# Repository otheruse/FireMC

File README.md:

This is FireMC, a motion controller for RepRap 3D printers and Factory Robots like FirePick delta and others. FireMC is currently implemented as an Arduino Due add-on board. FireMC features:
- 12-30V input
- Separate heatbed input
- 12v 1.5A switching regulator for 12v peripherals (if input is not 12v)
- 7 pwm channels (1 heatbed, 3 high power, 1 med power and 2 channels connected to the 12v rail)
- Sockets for 6 stepper drivers
- micro-sd socket
- WiFi via esp8266 module
- 5 thermistor inputs
- 7 limit switch inputs
- 4 io's which can be used for thermocouple inputs and/or servos
- 2 expansion headers for LCD or other peripherals

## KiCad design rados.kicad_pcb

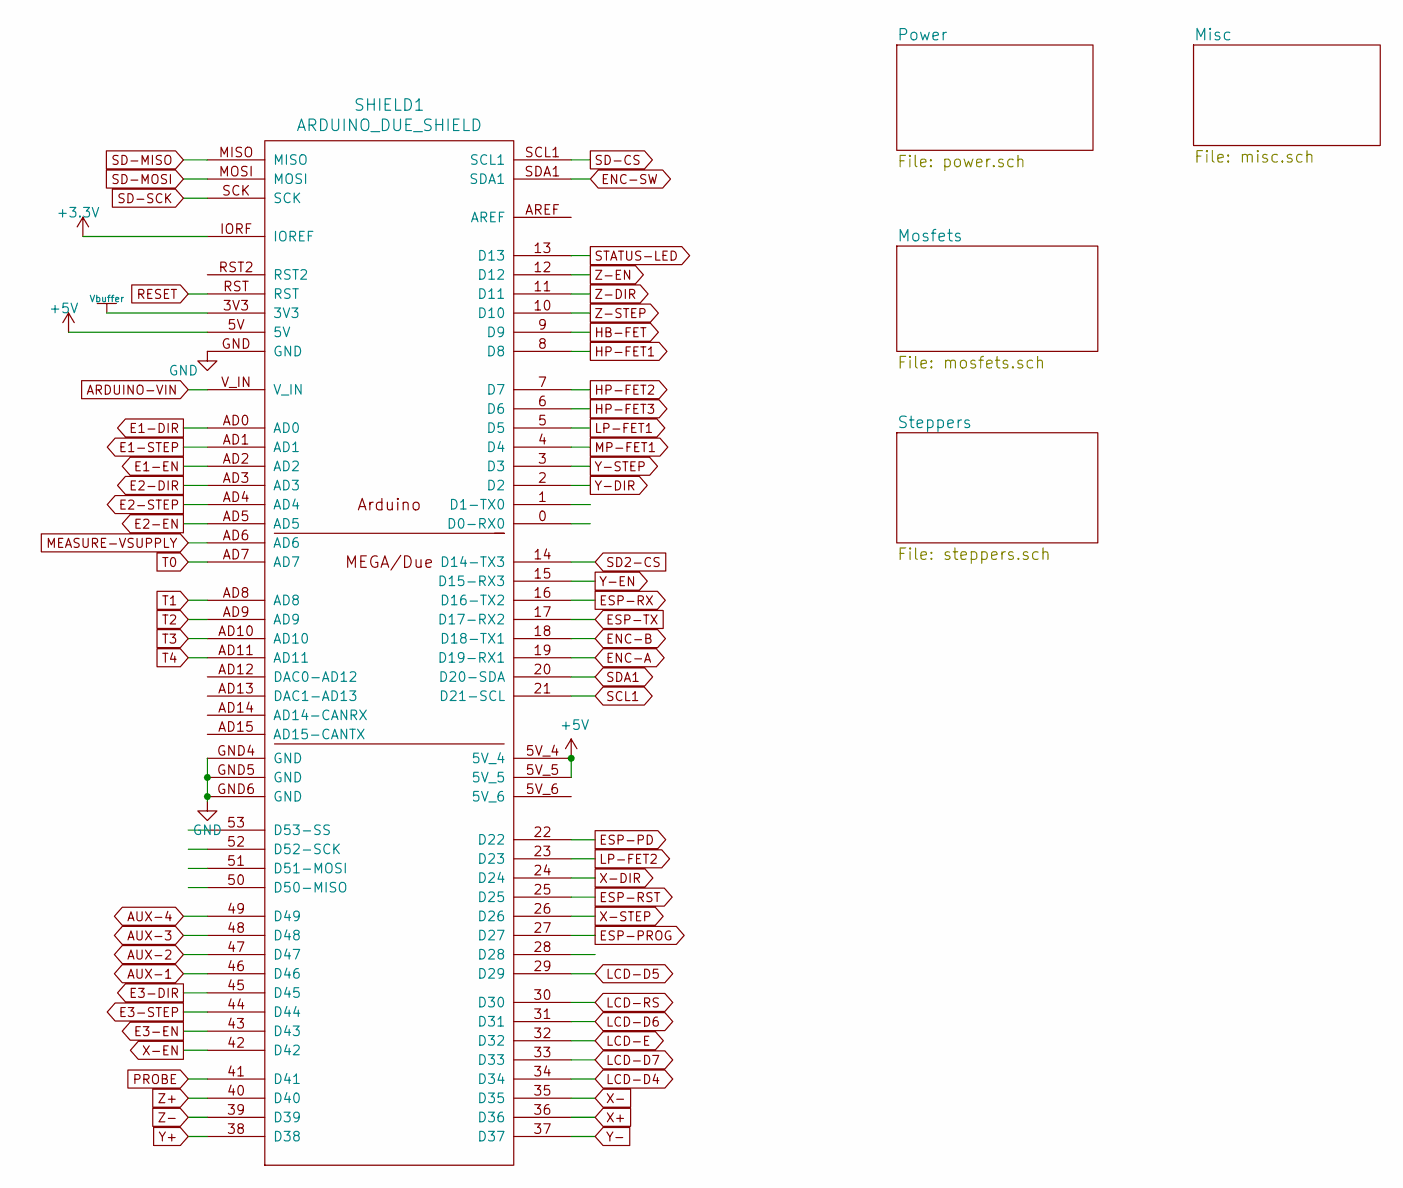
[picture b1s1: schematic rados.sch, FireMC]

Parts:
SHIELD1: ARDUINO_DUE_SHIELD; ARDUINO_MEGA_DUE_SHIELD_FOOTPRINT_OTH2

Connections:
+5V: SHIELD1.5V, SHIELD1.5V_4, SHIELD1.5V_5; also elsewhere on the board
ARDUINO-VIN: SHIELD1.V_IN; also elsewhere on the board
AUX-1: SHIELD1.46 (D46); also elsewhere on the board
AUX-2: SHIELD1.47 (D47); also elsewhere on the board
AUX-3: SHIELD1.48 (D48); also elsewhere on the board
AUX-4: SHIELD1.49 (D49); also elsewhere on the board
E1-DIR: SHIELD1.AD0; also elsewhere on the board
E1-EN: SHIELD1.AD2; also elsewhere on the board
E1-STEP: SHIELD1.AD1; also elsewhere on the board
E2-DIR: SHIELD1.AD3; also elsewhere on the board
E2-EN: SHIELD1.AD5; also elsewhere on the board
E2-STEP: SHIELD1.AD4; also elsewhere on the board
E3-DIR: SHIELD1.45 (D45); also elsewhere on the board
E3-EN: SHIELD1.43 (D43); also elsewhere on the board
E3-STEP: SHIELD1.44 (D44); also elsewhere on the board
ENC-A: SHIELD1.19 (D19-RX1); also elsewhere on the board
ENC-B: SHIELD1.18 (D18-TX1); also elsewhere on the board
ENC-SW: SHIELD1.SDA1; also elsewhere on the board
ESP-PD: SHIELD1.22 (D22); also elsewhere on the board
ESP-PROG: SHIELD1.27 (D27); also elsewhere on the board
ESP-RST: SHIELD1.25 (D25); also elsewhere on the board
ESP-RX: SHIELD1.16 (D16-TX2); also elsewhere on the board
ESP-TX: SHIELD1.17 (D17-RX2); also elsewhere on the board
GND: SHIELD1.GND, SHIELD1.GND4 (GND), SHIELD1.GND5 (GND), SHIELD1.GND6 (GND); also elsewhere on the board
HB-FET: SHIELD1.9 (D9); also elsewhere on the board
HP-FET1: SHIELD1.8 (D8); also elsewhere on the board
HP-FET2: SHIELD1.7 (D7); also elsewhere on the board
HP-FET3: SHIELD1.6 (D6); also elsewhere on the board
LCD-D4: SHIELD1.34 (D34); also elsewhere on the board
LCD-D5: SHIELD1.29 (D29); also elsewhere on the board
LCD-D6: SHIELD1.31 (D31); also elsewhere on the board
LCD-D7: SHIELD1.33 (D33); also elsewhere on the board
LCD-E: SHIELD1.32 (D32); also elsewhere on the board
LCD-RS: SHIELD1.30 (D30); also elsewhere on the board
LP-FET1: SHIELD1.5 (D5); also elsewhere on the board
LP-FET2: SHIELD1.23 (D23); also elsewhere on the board
MEASURE-VSUPPLY: SHIELD1.AD6; also elsewhere on the board
MP-FET1: SHIELD1.4 (D4); also elsewhere on the board
PROBE: SHIELD1.41 (D41); also elsewhere on the board
RESET: SHIELD1.RST; also elsewhere on the board
SCL1: SHIELD1.21 (D21-SCL); also elsewhere on the board
SD2-CS: SHIELD1.14 (D14-TX3); also elsewhere on the board
SD-CS: SHIELD1.SCL1; also elsewhere on the board
SD-MISO: SHIELD1.MISO; also elsewhere on the board
SD-MOSI: SHIELD1.MOSI; also elsewhere on the board
SD-SCK: SHIELD1.SCK; also elsewhere on the board
SDA1: SHIELD1.20 (D20-SDA); also elsewhere on the board
STATUS-LED: SHIELD1.13 (D13); also elsewhere on the board
T0: SHIELD1.AD7; also elsewhere on the board
T1: SHIELD1.AD8; also elsewhere on the board
T2: SHIELD1.AD9; also elsewhere on the board
T3: SHIELD1.AD10; also elsewhere on the board
T4: SHIELD1.AD11; also elsewhere on the board
Vbuffer: SHIELD1.3V3
X+: SHIELD1.36 (D36); also elsewhere on the board
X-: SHIELD1.35 (D35); also elsewhere on the board
X-DIR: SHIELD1.24 (D24); also elsewhere on the board
X-EN: SHIELD1.42 (D42); also elsewhere on the board
X-STEP: SHIELD1.26 (D26); also elsewhere on the board
Y+: SHIELD1.38 (D38); also elsewhere on the board
Y-: SHIELD1.37 (D37); also elsewhere on the board
Y-DIR: SHIELD1.2 (D2); also elsewhere on the board
Y-EN: SHIELD1.15 (D15-RX3); also elsewhere on the board
Y-STEP: SHIELD1.3 (D3); also elsewhere on the board
Z+: SHIELD1.40 (D40); also elsewhere on the board
Z-: SHIELD1.39 (D39); also elsewhere on the board
Z-DIR: SHIELD1.11 (D11); also elsewhere on the board
Z-EN: SHIELD1.12 (D12); also elsewhere on the board
Z-STEP: SHIELD1.10 (D10); also elsewhere on the board

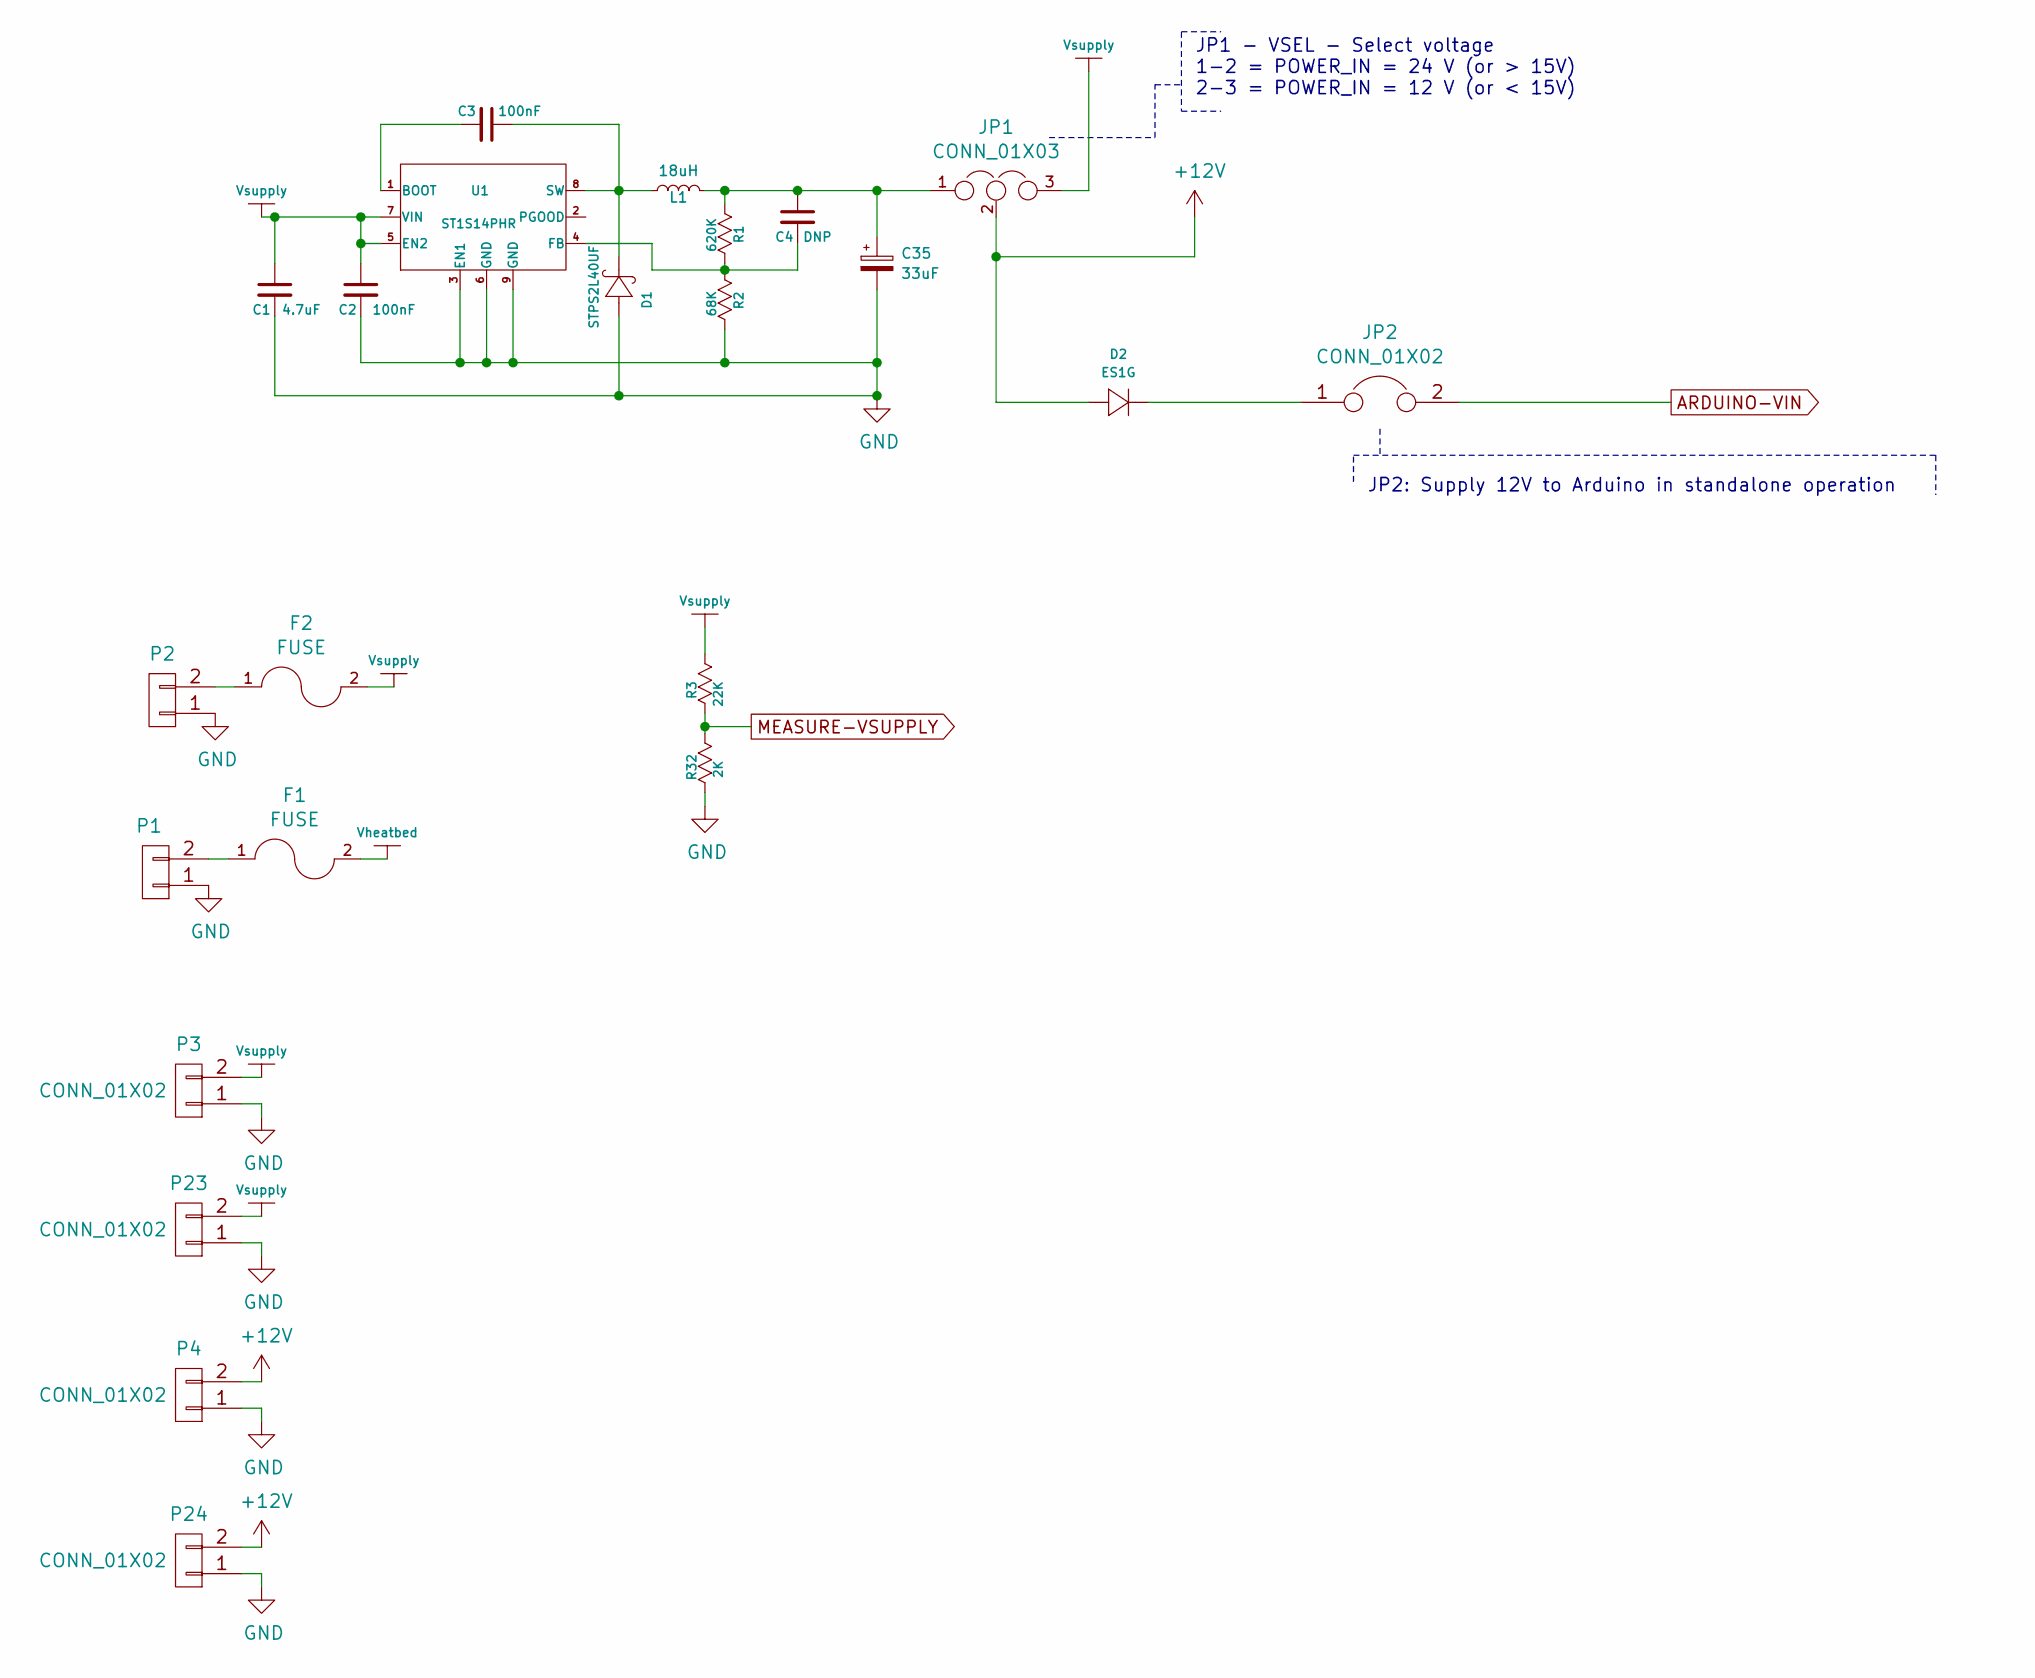
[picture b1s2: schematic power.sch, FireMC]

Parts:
C1: 4.7uF; C_1210; VoltageRating 50V
C2, C3: 100nF; C_0603; VoltageRating 50V
C4: DNP; C_0603
C35: 33uF; c_elec_6.3x7.7; VoltageRating 25V
D1: STPS2L40UF; DO214AA_SMB
D2: ES1G; DO214AC_SMA
F1, F2: FUSE; FUSEHOLDER_MINI_KEYSTONE_3557
JP1: CONN_01X03; CON_HDR_1x3_2.54mm
JP2: CONN_01X02; CON_HDR_1x2_2.54mm
L1: 18uH; INDUCTOR_BOURNS_RLB914
P1, P2: CONN_01X02; CON_PHOENIX_MSTBA-2.5-2-G-5.08
P3, P4, P23, P24: CONN_01X02; CON_HDR_1x2_2.54mm
R1: 620K; R_0603
R2: 68K; R_0603
R3: 22K; R_0603
R32: 2K; R_0603
U1: ST1S14PHR; HSOP8

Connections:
+12V: D2.2, JP1.2, P4.2, P24.2; also elsewhere on the board
ARDUINO-VIN: JP2.2; also elsewhere on the board
GND: C1.2, C2.2, C35.2, D1.2 (anode), P1.1, P2.1, P3.1, P4.1, P23.1, P24.1, R2.2, R32.2, U1.3 (EN1), U1.6 (GND), U1.9 (GND); also elsewhere on the board
MEASURE-VSUPPLY: R3.2, R32.1; also elsewhere on the board
unnamed: C3.1, D1.1 (cathode), L1.1, U1.8 (SW)
unnamed: C3.2, U1.1 (BOOT)
unnamed: C4.2, R1.2, R2.1, U1.4 (FB)
unnamed: C4.1, C35.1, JP1.1, L1.2, R1.1
unnamed: D2.1, JP2.1
unnamed: F1.1, P1.2
unnamed: F2.1, P2.2
Vheatbed: F1.2; also elsewhere on the board
Vsupply: C1.1, C2.1, F2.2, JP1.3, P3.2, P23.2, R3.1, U1.5 (EN2), U1.7 (VIN); also elsewhere on the board

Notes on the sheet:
JP1 - VSEL - Select voltage 1-2 = POWER_IN = 24 V (or > 15V) 2-3 = POWER_IN = 12 V (or < 15V)
JP2: Supply 12V to Arduino in standalone operation

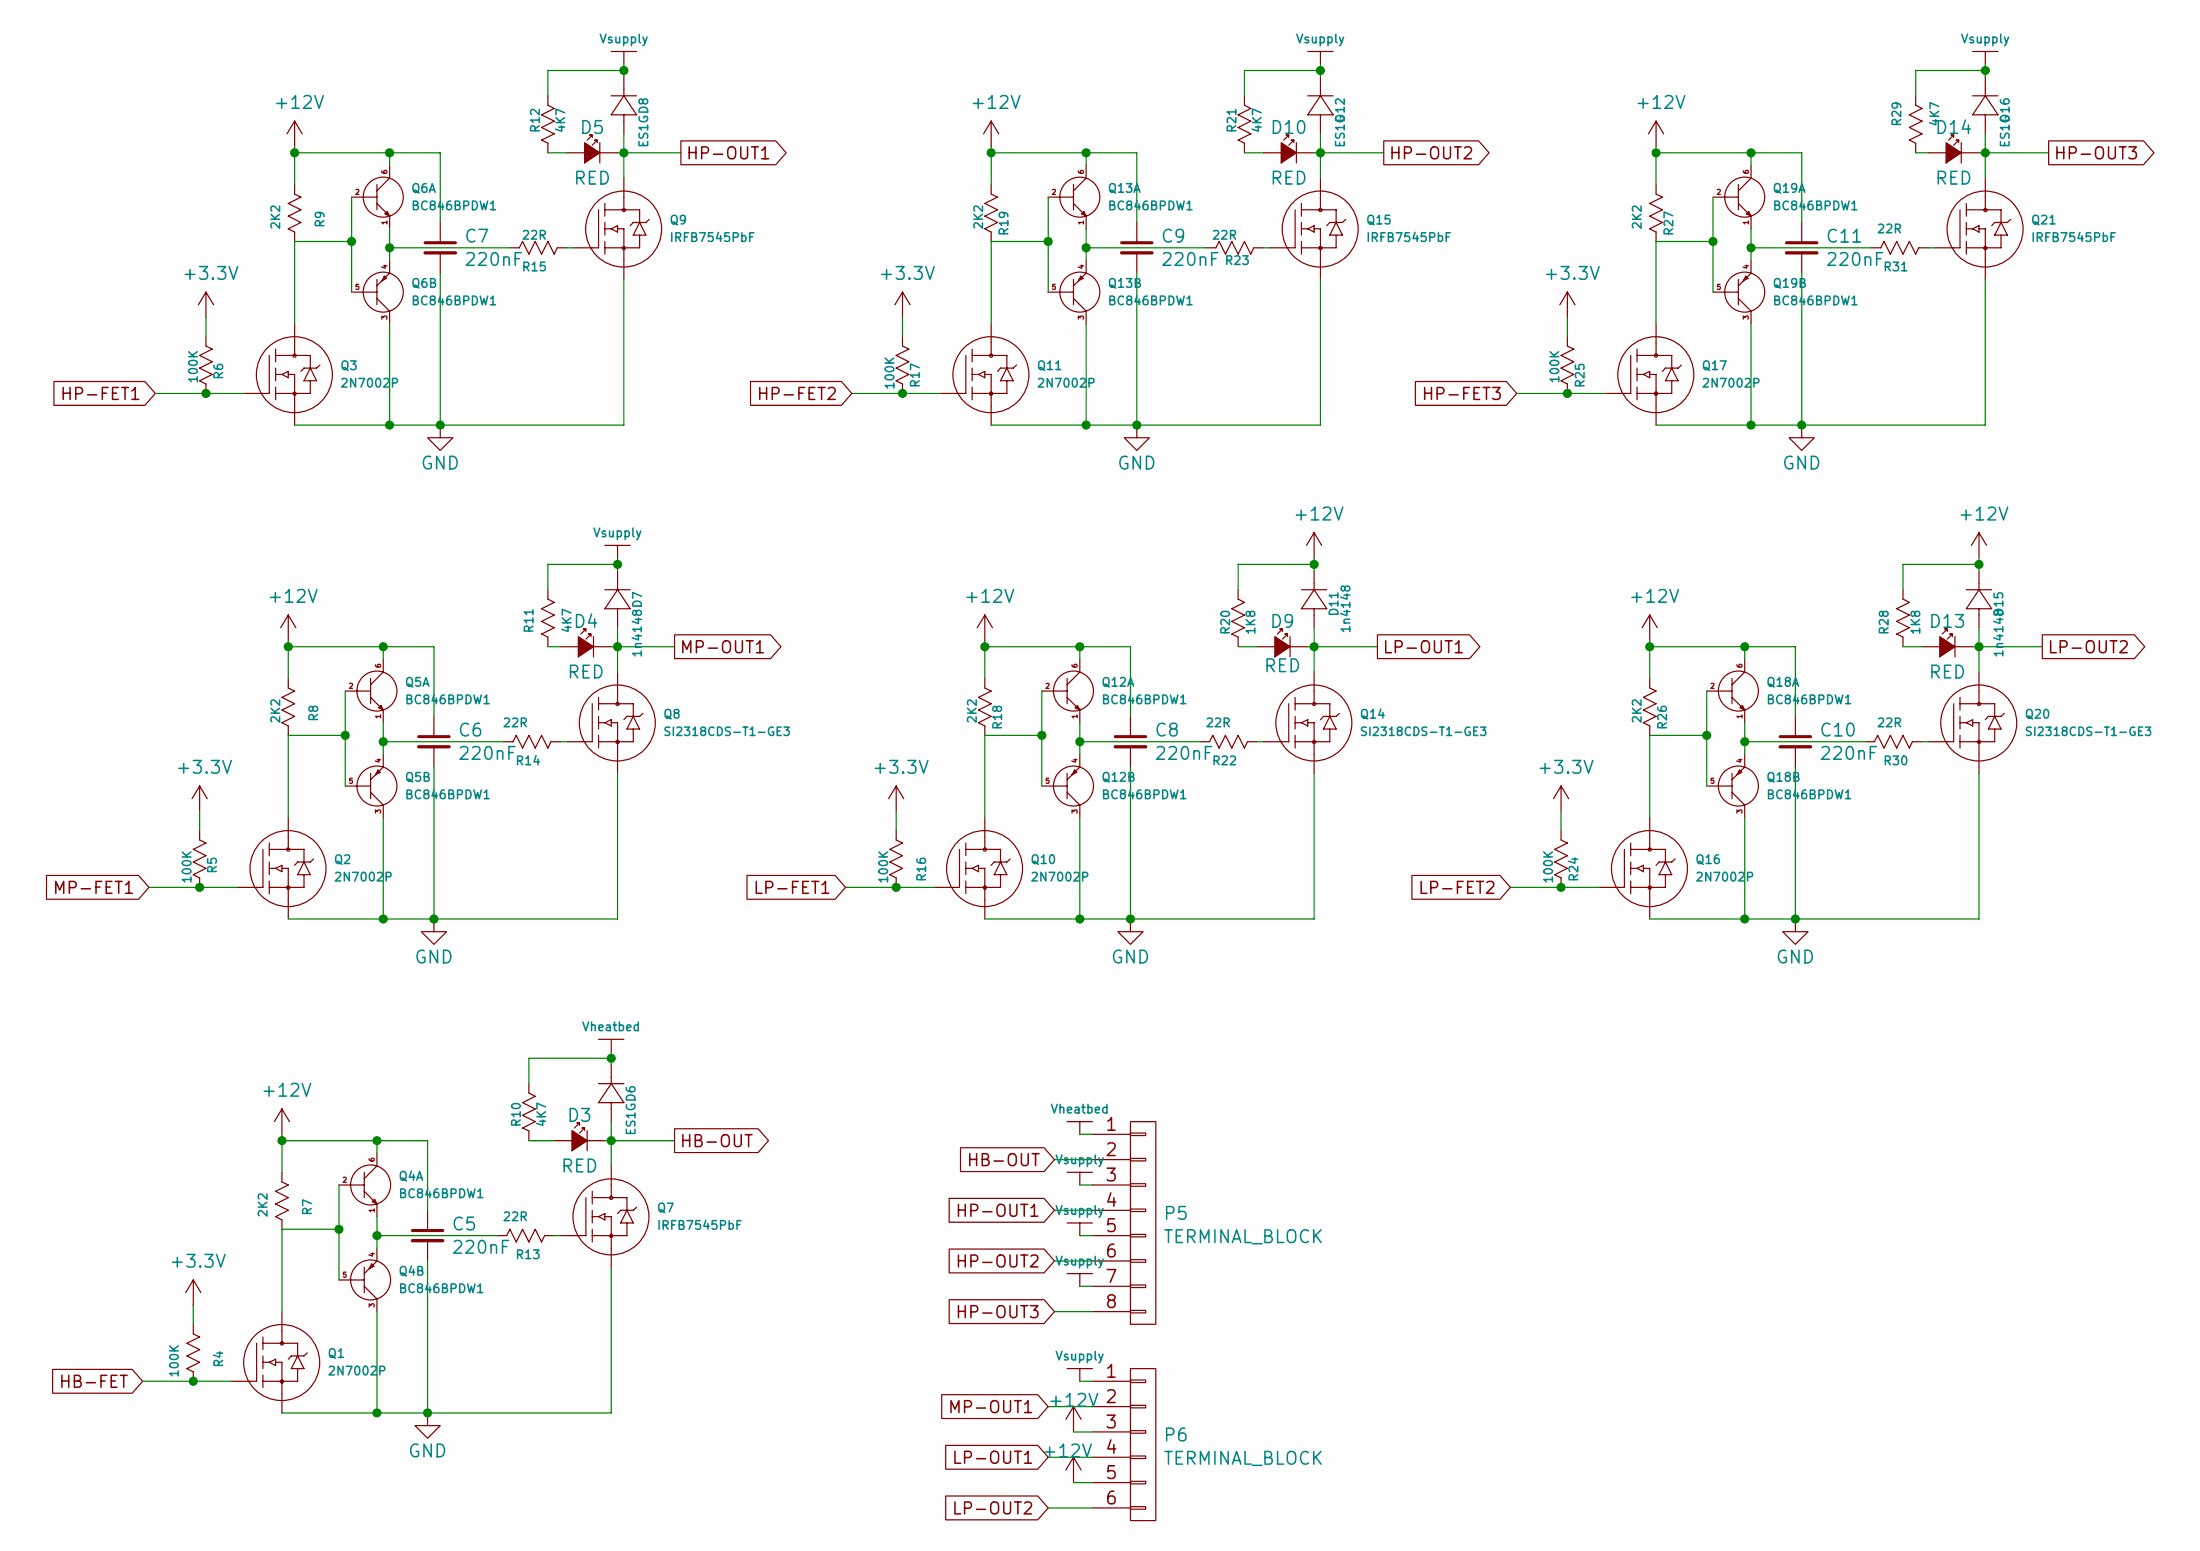
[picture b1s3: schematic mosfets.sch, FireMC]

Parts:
C5, C6, C7, C8, C9, C10, C11: 220nF; C_0603; VoltageRating 16V
D3, D4, D5, D9, D10, D13, D14: RED; LED-0603
D6, D8, D12, D16: ES1G; DO214AC_SMA
D7, D11, D15: 1n4148; DO213AA_SOD-80_MiniMelf
P5: TERMINAL_BLOCK; TERMINAL_BLOCK_8_PIN_5mm
P6: TERMINAL_BLOCK; TERMINAL_BLOCK_6_PIN_5mm
Q1, Q2, Q3, Q10, Q11, Q16, Q17: 2N7002P; SOT23_3L
Q4, Q5, Q6, Q12, Q13, Q18, Q19: BC846BPDW1; SC70_6L
Q7, Q9, Q15, Q21: IRFB7545PbF; TO-220-3
Q8, Q14, Q20: SI2318CDS-T1-GE3; SOT23_3L
R4, R5, R6, R16, R17, R24, R25: 100K; R_0603
R7, R8, R9, R18, R19, R26, R27: 2K2; R_0603
R10, R11, R12, R21, R29: 4K7; R_0805
R13, R14, R15, R22, R23, R30, R31: 22R; R_0603
R20, R28: 1K8; R_0603

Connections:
+12V: C5.1, C6.1, C7.1, C8.1, C9.1, C10.1, C11.1, D11.2, D15.2, P6.3, P6.5, Q4.6 (C), Q5.6 (C), Q6.6 (C), Q12.6 (C), Q13.6 (C), Q18.6 (C), Q19.6 (C), R7.2, R8.2, R9.2, R18.2, R19.2, R20.1, R26.2, R27.2, R28.1; also elsewhere on the board
GND: C5.2, C6.2, C7.2, C8.2, C9.2, C10.2, C11.2, Q1.2 (S), Q2.2 (S), Q3.2 (S), Q4.3 (C), Q5.3 (C), Q6.3 (C), Q7.3 (S), Q8.2 (S), Q9.3 (S), Q10.2 (S), Q11.2 (S), Q12.3 (C), Q13.3 (C), Q14.2 (S), Q15.3 (S), Q16.2 (S), Q17.2 (S), Q18.3 (C), Q19.3 (C), Q20.2 (S), Q21.3 (S); also elsewhere on the board
HB-FET: Q1.1 (G), R4.1; also elsewhere on the board
HB-OUT: D3.2 (K), D6.2, P5.2, Q7.2 (D)
HP-FET1: Q3.1 (G), R6.1; also elsewhere on the board
HP-FET2: Q11.1 (G), R17.1; also elsewhere on the board
HP-FET3: Q17.1 (G), R25.1; also elsewhere on the board
HP-OUT1: D5.2 (K), D8.2, P5.4, Q9.2 (D)
HP-OUT2: D10.2 (K), D12.2, P5.6, Q15.2 (D)
HP-OUT3: D14.2 (K), D16.2, P5.8, Q21.2 (D)
LP-FET1: Q10.1 (G), R16.1; also elsewhere on the board
LP-FET2: Q16.1 (G), R24.1; also elsewhere on the board
LP-OUT1: D9.2 (K), D11.1, P6.4, Q14.3 (D)
LP-OUT2: D13.2 (K), D15.1, P6.6, Q20.3 (D)
MP-FET1: Q2.1 (G), R5.1; also elsewhere on the board
MP-OUT1: D4.2 (K), D7.1, P6.2, Q8.3 (D)
unnamed: D3.1 (A), R10.2
unnamed: D4.1 (A), R11.2
unnamed: D5.1 (A), R12.2
unnamed: D9.1 (A), R20.2
unnamed: D10.1 (A), R21.2
unnamed: D13.1 (A), R28.2
unnamed: D14.1 (A), R29.2
unnamed: Q1.3 (D), Q4.2 (B), Q4.5 (B), R7.1
unnamed: Q2.3 (D), Q5.2 (B), Q5.5 (B), R8.1
unnamed: Q3.3 (D), Q6.2 (B), Q6.5 (B), R9.1
unnamed: Q4.1 (E), Q4.4 (E), R13.1
unnamed: Q5.1 (E), Q5.4 (E), R14.1
unnamed: Q6.1 (E), Q6.4 (E), R15.1
unnamed: Q7.1 (G), R13.2
unnamed: Q8.1 (G), R14.2
unnamed: Q9.1 (G), R15.2
unnamed: Q10.3 (D), Q12.2 (B), Q12.5 (B), R18.1
unnamed: Q11.3 (D), Q13.2 (B), Q13.5 (B), R19.1
unnamed: Q12.1 (E), Q12.4 (E), R22.1
unnamed: Q13.1 (E), Q13.4 (E), R23.1
unnamed: Q14.1 (G), R22.2
unnamed: Q15.1 (G), R23.2
unnamed: Q16.3 (D), Q18.2 (B), Q18.5 (B), R26.1
unnamed: Q17.3 (D), Q19.2 (B), Q19.5 (B), R27.1
unnamed: Q18.1 (E), Q18.4 (E), R30.1
unnamed: Q19.1 (E), Q19.4 (E), R31.1
unnamed: Q20.1 (G), R30.2
unnamed: Q21.1 (G), R31.2
Vheatbed: D6.1, P5.1, R10.1; also elsewhere on the board
Vsupply: D7.2, D8.1, D12.1, D16.1, P5.3, P5.5, P5.7, P6.1, R11.1, R12.1, R21.1, R29.1; also elsewhere on the board

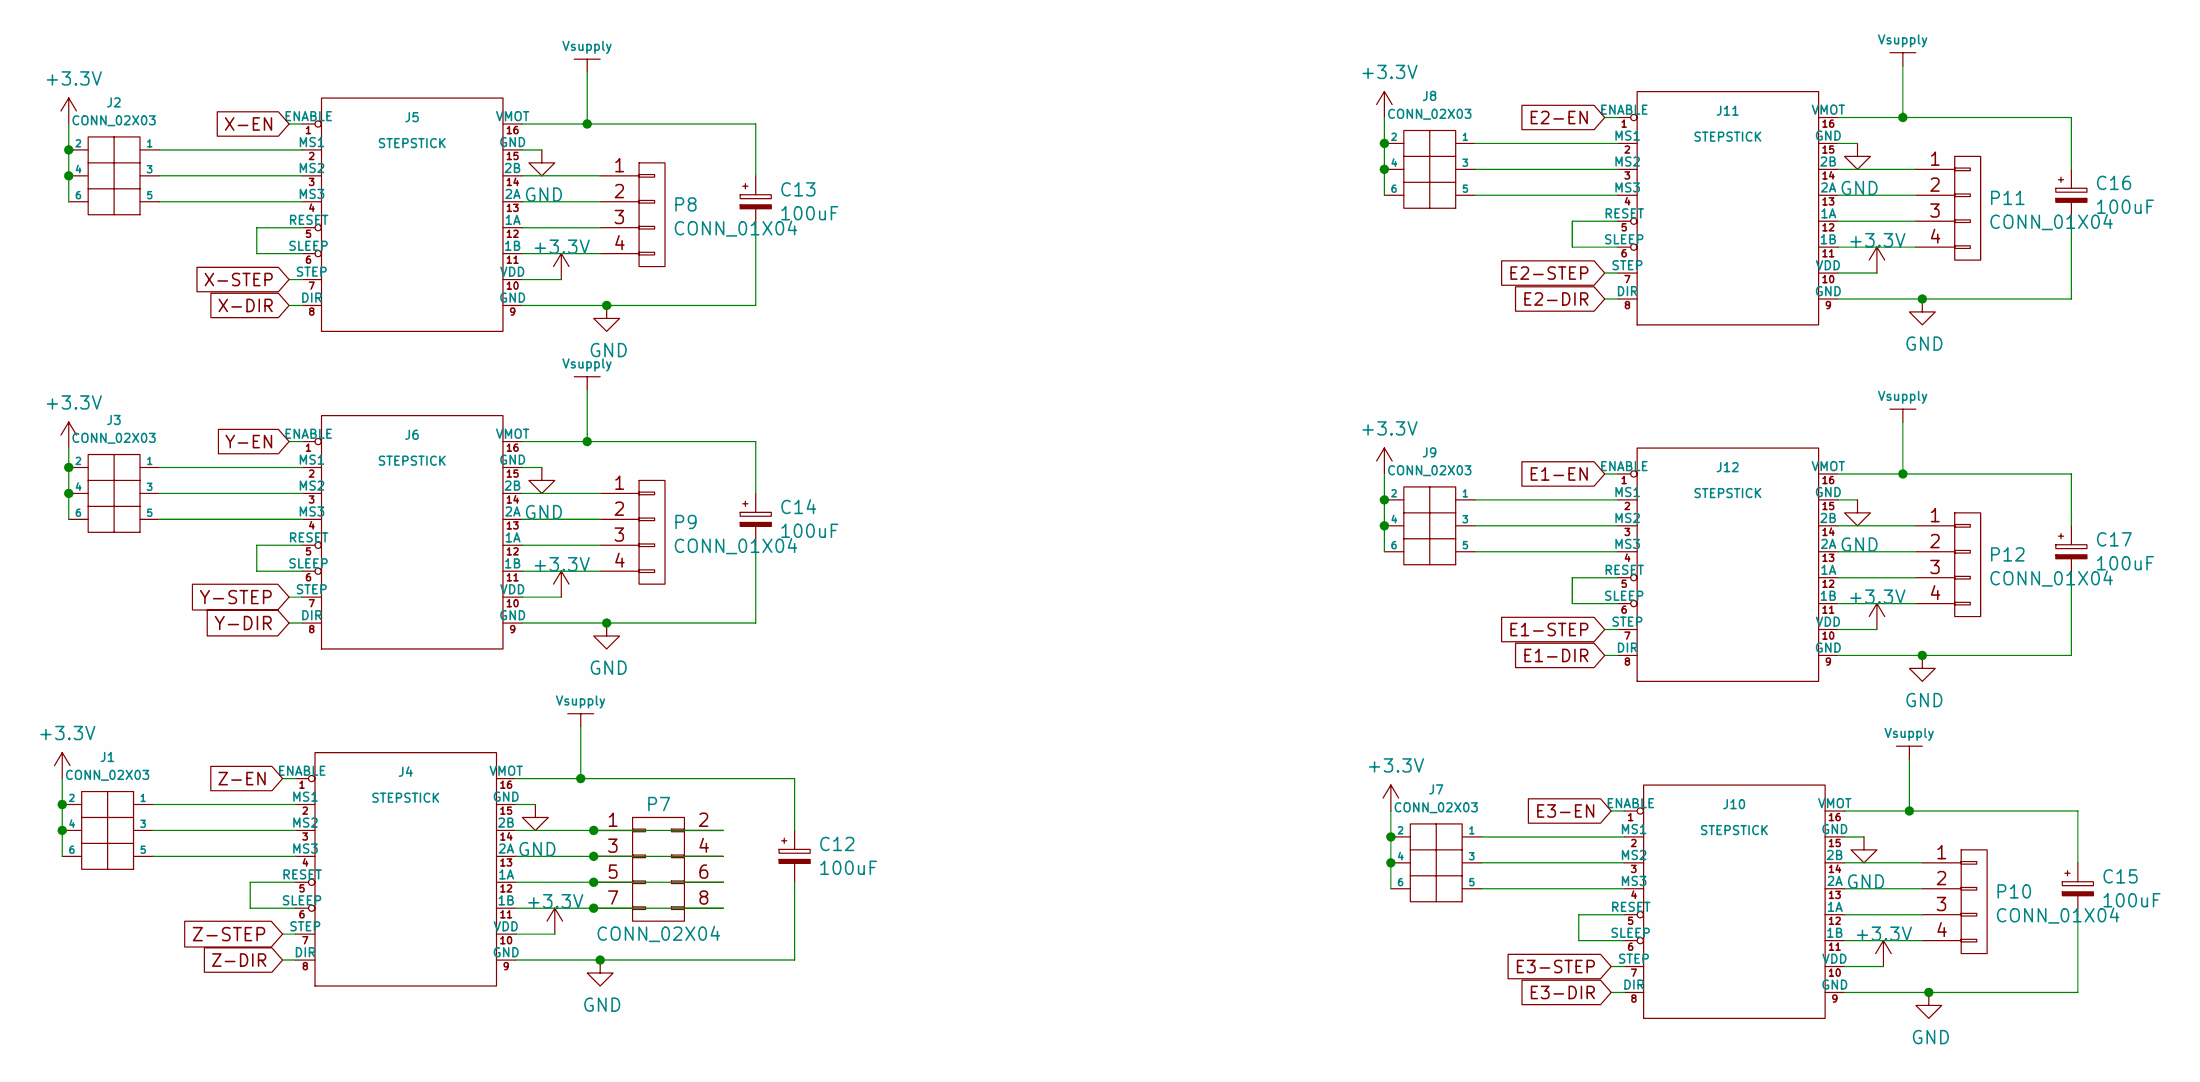
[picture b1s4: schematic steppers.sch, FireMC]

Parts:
C12, C13, C14, C15, C16, C17: 100uF; c_elec_6.3x7.7; VoltageRating 50V
J1, J2, J3, J7, J8, J9: CONN_02X03; CON_HDR_2x3_2.54mm
J4, J5, J6, J10, J11, J12: STEPSTICK
P7: CONN_02X04; CON_HDR_2x4_2.54mm
P8, P9, P10, P11, P12: CONN_01X04; CON_HDR_1x4_2.54mm

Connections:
E1-DIR: J12.8 (DIR); also elsewhere on the board
E1-EN: J12.1 (ENABLE); also elsewhere on the board
E1-STEP: J12.7 (STEP); also elsewhere on the board
E2-DIR: J11.8 (DIR); also elsewhere on the board
E2-EN: J11.1 (ENABLE); also elsewhere on the board
E2-STEP: J11.7 (STEP); also elsewhere on the board
E3-DIR: J10.8 (DIR); also elsewhere on the board
E3-EN: J10.1 (ENABLE); also elsewhere on the board
E3-STEP: J10.7 (STEP); also elsewhere on the board
GND: C12.2, C13.2, C14.2, C15.2, C16.2, C17.2, J4.9 (GND), J4.15 (GND), J5.9 (GND), J5.15 (GND), J6.9 (GND), J6.15 (GND), J10.9 (GND), J10.15 (GND), J11.9 (GND), J11.15 (GND), J12.9 (GND), J12.15 (GND); also elsewhere on the board
unnamed: J1.1, J4.2 (MS1)
unnamed: J1.3, J4.3 (MS2)
unnamed: J1.5, J4.4 (MS3)
unnamed: J2.1, J5.2 (MS1)
unnamed: J2.3, J5.3 (MS2)
unnamed: J2.5, J5.4 (MS3)
unnamed: J3.1, J6.2 (MS1)
unnamed: J3.3, J6.3 (MS2)
unnamed: J3.5, J6.4 (MS3)
unnamed: J4.5 (RESET), J4.6 (SLEEP)
unnamed: J4.11 (1B), P7.7, P7.8
unnamed: J4.12 (1A), P7.5, P7.6
unnamed: J4.13 (2A), P7.3, P7.4
unnamed: J4.14 (2B), P7.1, P7.2
unnamed: J5.5 (RESET), J5.6 (SLEEP)
unnamed: J5.11 (1B), P8.4
unnamed: J5.12 (1A), P8.3
unnamed: J5.13 (2A), P8.2
unnamed: J5.14 (2B), P8.1
unnamed: J6.5 (RESET), J6.6 (SLEEP)
unnamed: J6.11 (1B), P9.4
unnamed: J6.12 (1A), P9.3
unnamed: J6.13 (2A), P9.2
unnamed: J6.14 (2B), P9.1
unnamed: J7.1, J10.2 (MS1)
unnamed: J7.3, J10.3 (MS2)
unnamed: J7.5, J10.4 (MS3)
unnamed: J10.5 (RESET), J10.6 (SLEEP)
unnamed: J10.11 (1B), P10.4
unnamed: J10.12 (1A), P10.3
unnamed: J10.13 (2A), P10.2
unnamed: J10.14 (2B), P10.1
unnamed: J8.1, J11.2 (MS1)
unnamed: J8.3, J11.3 (MS2)
unnamed: J8.5, J11.4 (MS3)
unnamed: J11.5 (RESET), J11.6 (SLEEP)
unnamed: J11.11 (1B), P11.4
unnamed: J11.12 (1A), P11.3
unnamed: J11.13 (2A), P11.2
unnamed: J11.14 (2B), P11.1
unnamed: J9.1, J12.2 (MS1)
unnamed: J9.3, J12.3 (MS2)
unnamed: J9.5, J12.4 (MS3)
unnamed: J12.5 (RESET), J12.6 (SLEEP)
unnamed: J12.11 (1B), P12.4
unnamed: J12.12 (1A), P12.3
unnamed: J12.13 (2A), P12.2
unnamed: J12.14 (2B), P12.1
Vsupply: C12.1, C13.1, C14.1, C15.1, C16.1, C17.1, J4.16 (VMOT), J5.16 (VMOT), J6.16 (VMOT), J10.16 (VMOT), J11.16 (VMOT), J12.16 (VMOT); also elsewhere on the board
X-DIR: J5.8 (DIR); also elsewhere on the board
X-EN: J5.1 (ENABLE); also elsewhere on the board
X-STEP: J5.7 (STEP); also elsewhere on the board
Y-DIR: J6.8 (DIR); also elsewhere on the board
Y-EN: J6.1 (ENABLE); also elsewhere on the board
Y-STEP: J6.7 (STEP); also elsewhere on the board
Z-DIR: J4.8 (DIR); also elsewhere on the board
Z-EN: J4.1 (ENABLE); also elsewhere on the board
Z-STEP: J4.7 (STEP); also elsewhere on the board

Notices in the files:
parts and their libraries:
GPL
